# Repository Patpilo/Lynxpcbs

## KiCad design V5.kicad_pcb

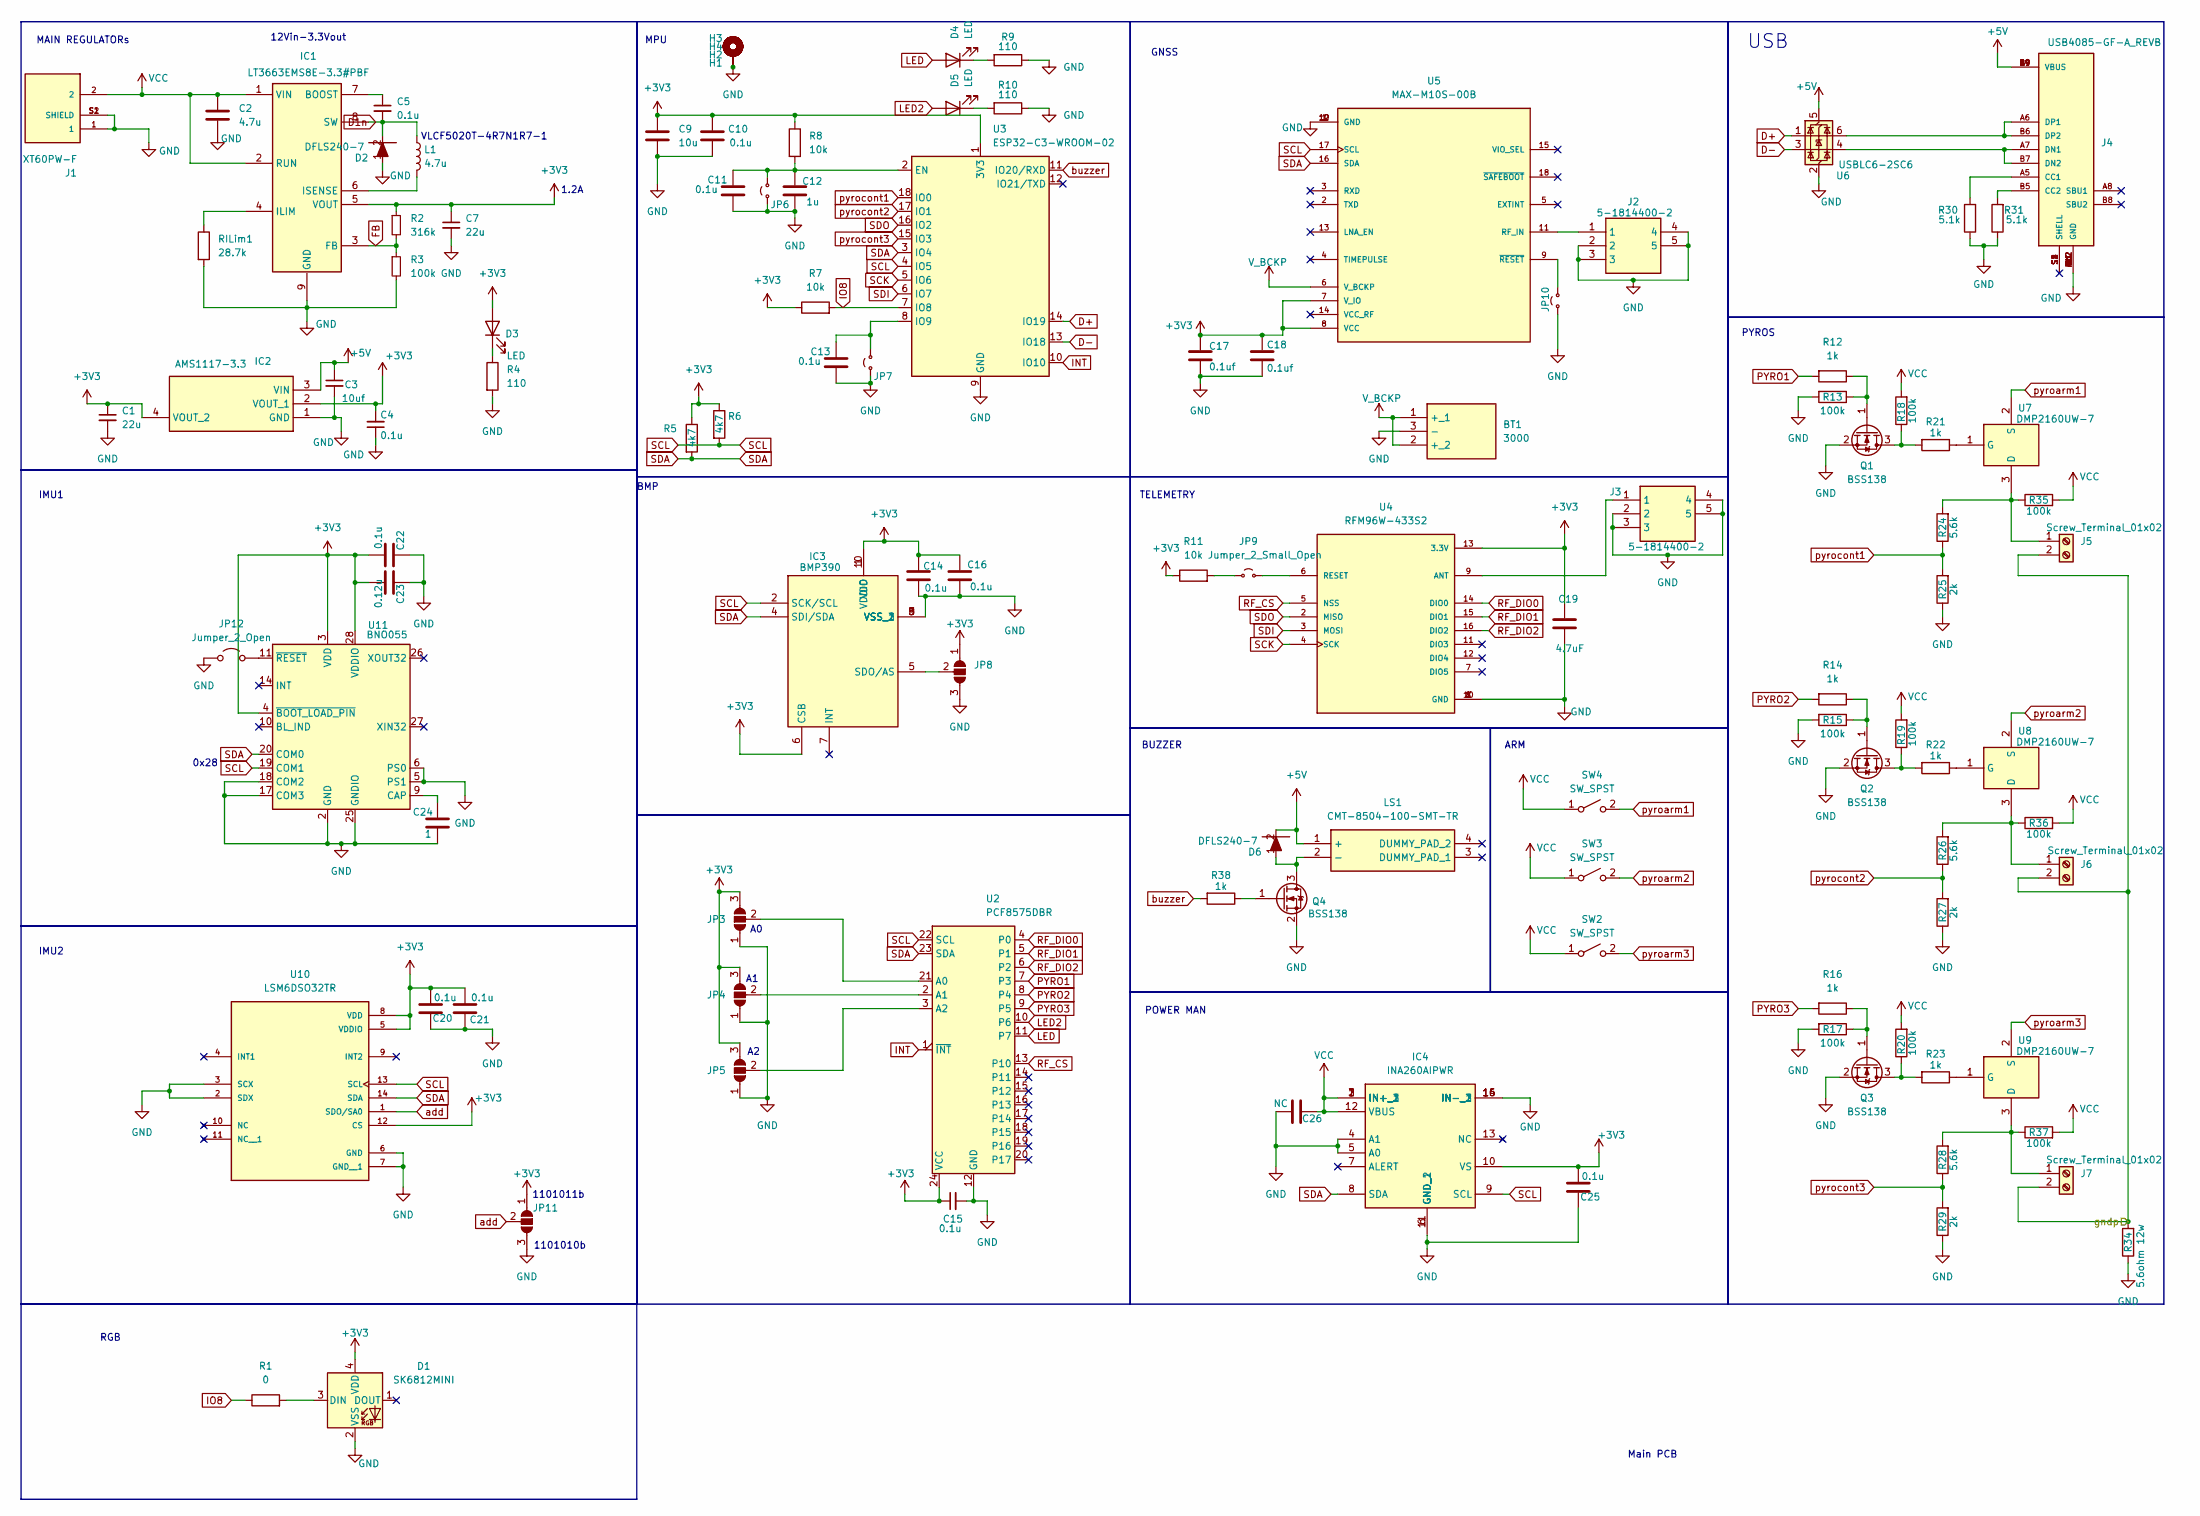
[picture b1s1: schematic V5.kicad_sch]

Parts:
BT1: 3000; Manufacturer_Part_Number 3000; Mouser Part Number 534-3000
C1: 22u; C_0805_2012Metric_Pad1.18x1.45mm_HandSolder
C2: 4.7u; C_1206_3216Metric_Pad1.33x1.80mm_HandSolder
C3: 10uf; C_0805_2012Metric_Pad1.18x1.45mm_HandSolder
C4, C5, C10, C11, C13, C14, C15, C16, C21: 0.1u; C_0805_2012Metric_Pad1.18x1.45mm_HandSolder
C7: 22u; C_1206_3216Metric_Pad1.33x1.80mm_HandSolder
C9: 10u; C_0805_2012Metric_Pad1.18x1.45mm_HandSolder
C12: 1u; C_0805_2012Metric_Pad1.18x1.45mm_HandSolder
C17, C18: 0.1uf; C_0805_2012Metric_Pad1.18x1.45mm_HandSolder
C19: 4.7uF; C_1206_3216Metric_Pad1.33x1.80mm_HandSolder
C20, C22, C25: 0.1u; C_0201_0603Metric_Pad0.64x0.40mm_HandSolder
C23: 0.12u; C_0201_0603Metric_Pad0.64x0.40mm_HandSolder
C24: 1; C_0805_2012Metric_Pad1.18x1.45mm_HandSolder
C26: NC; C_0201_0603Metric_Pad0.64x0.40mm_HandSolder
D1: SK6812MINI; LED_SK6812MINI_PLCC4_3.5x3.5mm_P1.75mm
D2, D6: DFLS240-7; POWERDI123; Manufacturer_Part_Number DFLS240-7; Mouser Part Number 621-DFLS240-7
D3, D4, D5: LED; LED_0805_2012Metric_Pad1.15x1.40mm_HandSolder
H1, H2, H3, H4: MountingHole_Pad; MountingHole_2.7mm_M2.5_Pad_Via
IC1: LT3663EMS8E-3.3#PBF; SOP65P490X110-9N; Manufacturer_Part_Number LT3663EMS8E-3.3#PBF; Mouser Part Number 584-3663EMS8E-3.3PBF
IC2: AMS1117-3.3; SOT229P700X180-4N; Manufacturer_Part_Number AMS1117-3.3
IC3: BMP390; Manufacturer_Part_Number BMP390; Mouser Part Number 262-BMP390
IC4: INA260AIPWR; SOP65P640X120-16N; Manufacturer_Part_Number INA260AIPWR; Mouser Part Number 595-INA260AIPWR
J1: XT60PW-F; AMASS_XT60PW-F; PARTREV V1.2
J2, J3: 5-1814400-2; 518144002; Manufacturer_Part_Number 5-1814400-2; Mouser Part Number 571-5-1814400-2
J4: USB4085-GF-A_REVB; GCT_USB4085-GF-A_REVB; PARTREV B
J5, J6, J7: Screw_Terminal_01x02; 2828362
JP3, JP4, JP5, JP8, JP11: SolderJumper_3_Open; SolderJumper-3_P1.3mm_Open_RoundedPad1.0x1.5mm_NumberLabels
JP6, JP7, JP9, JP10: Jumper_2_Small_Open; SolderJumper-2_P1.3mm_Open_RoundedPad1.0x1.5mm
JP12: Jumper_2_Open; SolderJumper-2_P1.3mm_Open_RoundedPad1.0x1.5mm
L1: 4.7u; VLCF5020
LS1: CMT-8504-100-SMT-TR; CMT8504100SMTTR; Manufacturer_Part_Number CMT-8504-100-SMT-TR; Mouser Part Number 490-CMT-8504100SMTTR
Q1, Q2, Q3, Q4: BSS138; SOT-23
R1: 0; R_0805_2012Metric_Pad1.20x1.40mm_HandSolder
R2: 316k; R_0805_2012Metric_Pad1.20x1.40mm_HandSolder
R3, R13, R15, R17, R18, R19, R20: 100k; R_0805_2012Metric_Pad1.20x1.40mm_HandSolder
R4, R9, R10: 110; R_0805_2012Metric_Pad1.20x1.40mm_HandSolder
R5, R6: 4k7; R_0805_2012Metric_Pad1.20x1.40mm_HandSolder
R7, R8, R11: 10k; R_0805_2012Metric_Pad1.20x1.40mm_HandSolder
R12, R14, R16, R21, R22, R23: 1k; R_0402_1005Metric_Pad0.72x0.64mm_HandSolder
R24, R26, R28: 5.6k; R_0402_1005Metric_Pad0.72x0.64mm_HandSolder
R25, R27, R29: 2k; R_0402_1005Metric_Pad0.72x0.64mm_HandSolder
R30, R31: 5.1k; R_0402_1005Metric_Pad0.72x0.64mm_HandSolder
R34: 5.6ohm 12w; R_2512_6332Metric_Pad1.40x3.35mm_HandSolder
R35, R36, R37: 100k; R_0603_1608Metric_Pad0.98x0.95mm_HandSolder
R38: 1k; R_0805_2012Metric_Pad1.20x1.40mm_HandSolder
RILim1: 28.7k; R_0805_2012Metric_Pad1.20x1.40mm_HandSolder
SW2, SW3, SW4: SW_SPST; ET02MD1CBE
U2: PCF8575DBR; SSOP-24_5.3x8.2mm_P0.65mm
U3: ESP32-C3-WROOM-02
U4: RFM96W-433S2; MODULE_RFM96W-433S2; PARTREV 2.0
U5: MAX-M10S-00B; XCVR_MAX-M10S-00B; PARTREV C1
U6: USBLC6-2SC6; SOT-23-6
U7, U8, U9: DMP2160UW-7; SOT65P210X110-3N; Manufacturer_Part_Number DMP2160UW-7; Mouser Part Number 621-DMP2160UW-7
U10: LSM6DSO32TR; LGA-14L_2P5X3X0P83_STM; PARTREV 1
U11: BNO055; LGA-28_5.2x3.8mm_P0.5mm

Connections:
+3V3: C1.1, C4.2, C7.1, C9.1, C10.1, C14.1, C15.1, C16.1, C17.1, C18.1, C19.1, C20.1, C21.1, C22.1, C23.1, C25.1, D1.4 (VDD), D3.2 (A), IC1.5 (VOUT), IC2.2 (VOUT_1), IC2.4 (VOUT_2), IC3.1 (VDDIO), IC3.6 (CSB), IC3.10 (VDD), IC4.10 (VS), JP3.3 (B), JP4.3 (B), JP5.3 (B), JP8.1 (A), JP11.1 (A), R2.1, R5.1, R6.1, R7.1, R8.1, R11.1, U2.24 (VCC), U3.1 (3V3), U4.13 (3.3V), U5.7 (V_IO), U5.8 (VCC), U10.5 (VDDIO), U10.8 (VDD), U10.12 (CS), U11.3 (VDD), U11.4 (~BOOT_LOAD_PIN), U11.28 (VDDIO)
+5V: C3.1, D6.2 (K), IC2.3 (VIN), J4.A4 (VBUS), J4.A9 (VBUS), J4.B4 (VBUS), J4.B9 (VBUS), LS1.1 (+), U6.5 (VBUS)
/gndp: J5.2, J6.2, J7.2, R34.2
D1n: C5.2, D2.2 (K), IC1.8 (SW), L1.1
D+: U3.14 (IO19), U6.1 (I/O1)
D-: U3.13 (IO18), U6.3 (I/O2)
FB: IC1.3 (FB), R2.2, R3.1
GND: BT1.3 (-), C1.2, C2.2, C3.2, C4.1, C7.2, C9.2, C10.2, C11.2, C12.2, C13.2, C14.2, C15.2, C16.2, C17.2, C18.2, C19.2, C20.2, C21.2, C22.2, C23.2, C24.1, C25.2, C26.1, D1.2 (VSS), D2.1 (A), H1.1, H2.1, H3.1, H4.1, IC1.9 (GND), IC2.1 (GND), IC3.3 (VSS_1), IC3.8 (VSS_2), IC3.9 (VSS_3), IC4.4 (A1), IC4.5 (A0), IC4.6 (GND_1), IC4.11 (GND_2), IC4.14 (IN-_1), IC4.15 (IN-_2), IC4.16 (IN-_3), J1.1, J1.S1 (SHIELD), J1.S2 (SHIELD), J2.2, J2.3, J2.4, J2.5, J3.2, J3.3, J3.4, J3.5, J4.A1 (GND), J4.A12 (GND), J4.B1 (GND), J4.B12 (GND), JP3.1 (A), JP4.1 (A), JP5.1 (A), JP6.1 (A), JP7.1 (A), JP8.3 (B), JP10.1 (A), JP11.3 (B), JP12.1 (A), Q1.2 (S), Q2.2 (S), Q3.2 (S), Q4.2 (S), R3.2, R4.2, R9.1, R10.1, R13.2, R15.2, R17.2, R25.1, R27.1, R29.1, R30.1, R31.1, R34.1, RILim1.2, U2.12 (GND), U3.9 (GND), U3.19 (GND), U4.1 (GND), U4.8 (GND), U4.10 (GND), U5.1 (GND), U5.10 (GND), U5.12 (GND), U6.2 (GND), U10.2 (SDX), U10.3 (SCX), U10.6 (GND), U10.7 (GND__1), U11.2 (GND), U11.5 (PS1), U11.6 (PS0), U11.17 (COM3), U11.18 (COM2), U11.25 (GNDIO)
INT: U2.1 (~INT), U3.10 (IO10)
IO8: R1.1, R7.2, U3.7 (IO8)
LED: D4.2 (A), U2.11 (P7)
LED2: D5.2 (A), U2.10 (P6)
unnamed: D1.3 (DIN), R1.2
unnamed: D3.1 (K), R4.1
unnamed: D4.1 (K), R9.2
unnamed: D5.1 (K), R10.2
unnamed: D6.1 (A), LS1.2 (-), Q4.3 (D)
unnamed: C5.1, IC1.7 (BOOST)
unnamed: IC1.4 (ILIM), RILim1.1
unnamed: IC1.6 (ISENSE), L1.2
unnamed: IC3.5 (SDO/AS), JP8.2 (C)
unnamed: J4.A5 (CC1), R30.2
unnamed: J4.B5 (CC2), R31.2
unnamed: J4.A7 (DN1), J4.B7 (DN2), U6.4 (I/O2)
unnamed: J4.A6 (DP1), J4.B6 (DP2), U6.6 (I/O1)
unnamed: J5.1, R24.2, R35.1, U7.3 (D)
unnamed: J6.1, R26.2, R36.1, U8.3 (D)
unnamed: J7.1, R28.2, R37.1, U9.3 (D)
unnamed: JP3.2 (C), U2.21 (A0)
unnamed: JP4.2 (C), U2.2 (A1)
unnamed: JP5.2 (C), U2.3 (A2)
unnamed: C11.1, C12.1, JP6.2 (B), R8.2, U3.2 (EN)
unnamed: C13.1, JP7.2 (B), U3.8 (IO9)
unnamed: JP9.1 (A), R11.2
unnamed: JP9.2 (B), U4.6 (RESET)
unnamed: JP10.2 (B), U5.9 (~RESET)
unnamed: JP12.2 (B), U11.11 (~RESET)
unnamed: Q1.3 (D), R18.1, R21.2
unnamed: Q1.1 (G), R12.1, R13.1
unnamed: Q2.3 (D), R19.1, R22.2
unnamed: Q2.1 (G), R14.1, R15.1
unnamed: Q3.3 (D), R20.1, R23.2
unnamed: Q3.1 (G), R16.1, R17.1
unnamed: Q4.1 (G), R38.1
unnamed: J3.1, U4.9 (ANT)
unnamed: J2.1, U5.11 (RF_IN)
unnamed: R21.1, U7.1 (G)
unnamed: R22.1, U8.1 (G)
unnamed: R23.1, U9.1 (G)
unnamed: C24.2, U11.9 (CAP)
PYRO1: R12.2, U2.7 (P3)
PYRO2: R14.2, U2.8 (P4)
PYRO3: R16.2, U2.9 (P5)
RF_CS: U2.13 (P10), U4.5 (NSS)
RF_DIO0: U2.4 (P0), U4.14 (DIO0)
RF_DIO1: U2.5 (P1), U4.15 (DIO1)
RF_DIO2: U2.6 (P2), U4.16 (DIO2)
SCK: U3.5 (IO6), U4.4 (SCK)
SCL: IC3.2 (SCK/SCL), IC4.9 (SCL), R6.2, U2.22 (SCL), U3.4 (IO5), U5.17 (SCL), U10.13 (SCL), U11.19 (COM1)
SDA: IC3.4 (SDI/SDA), IC4.8 (SDA), R5.2, U2.23 (SDA), U3.3 (IO4), U5.16 (SDA), U10.14 (SDA), U11.20 (COM0)
SDI: U3.6 (IO7), U4.3 (MOSI)
SDO: U3.16 (IO2), U4.2 (MISO)
VCC: C2.1, C26.2, IC1.1 (VIN), IC1.2 (RUN), IC4.1 (IN+_1), IC4.2 (IN+_2), IC4.3 (IN+_3), IC4.12 (VBUS), J1.2, R18.2, R19.2, R20.2, R35.2, R36.2, R37.2, SW2.1 (A), SW3.1 (A), SW4.1 (A)
V_BCKP: BT1.1 (+_1), BT1.2 (+_2), U5.6 (V_BCKP)
add: JP11.2 (C), U10.1 (SDO/SA0)
buzzer: R38.2, U3.11 (IO20/RXD)
pyroarm1: SW4.2 (B), U7.2 (S)
pyroarm2: SW3.2 (B), U8.2 (S)
pyroarm3: SW2.2 (B), U9.2 (S)
pyrocont1: R24.1, R25.2, U3.18 (IO0)
pyrocont2: R26.1, R27.2, U3.17 (IO1)
pyrocont3: R28.1, R29.2, U3.15 (IO3)

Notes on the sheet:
IMU2
0x28
POWER MAN
1101010b
MPU
PYROS
1.2A
ARM
12Vin-3.3Vout
Main PCB
IMU1
BMP
TELEMETRY
GNSS
BUZZER
1101011b
RGB
VLCF5020T-4R7N1R7-1
MAIN REGULATORs
USB

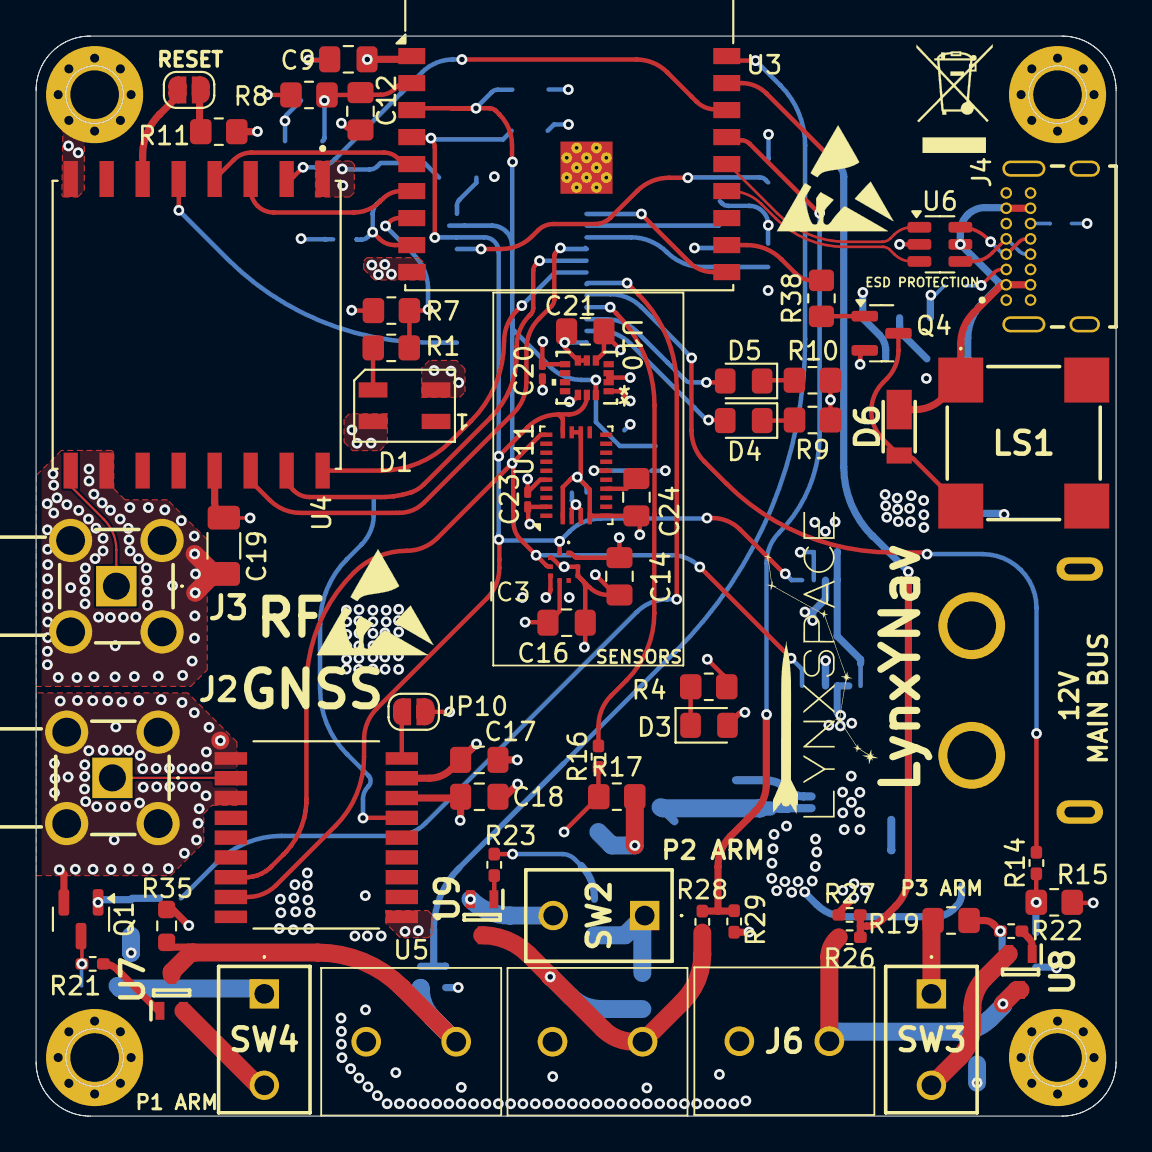
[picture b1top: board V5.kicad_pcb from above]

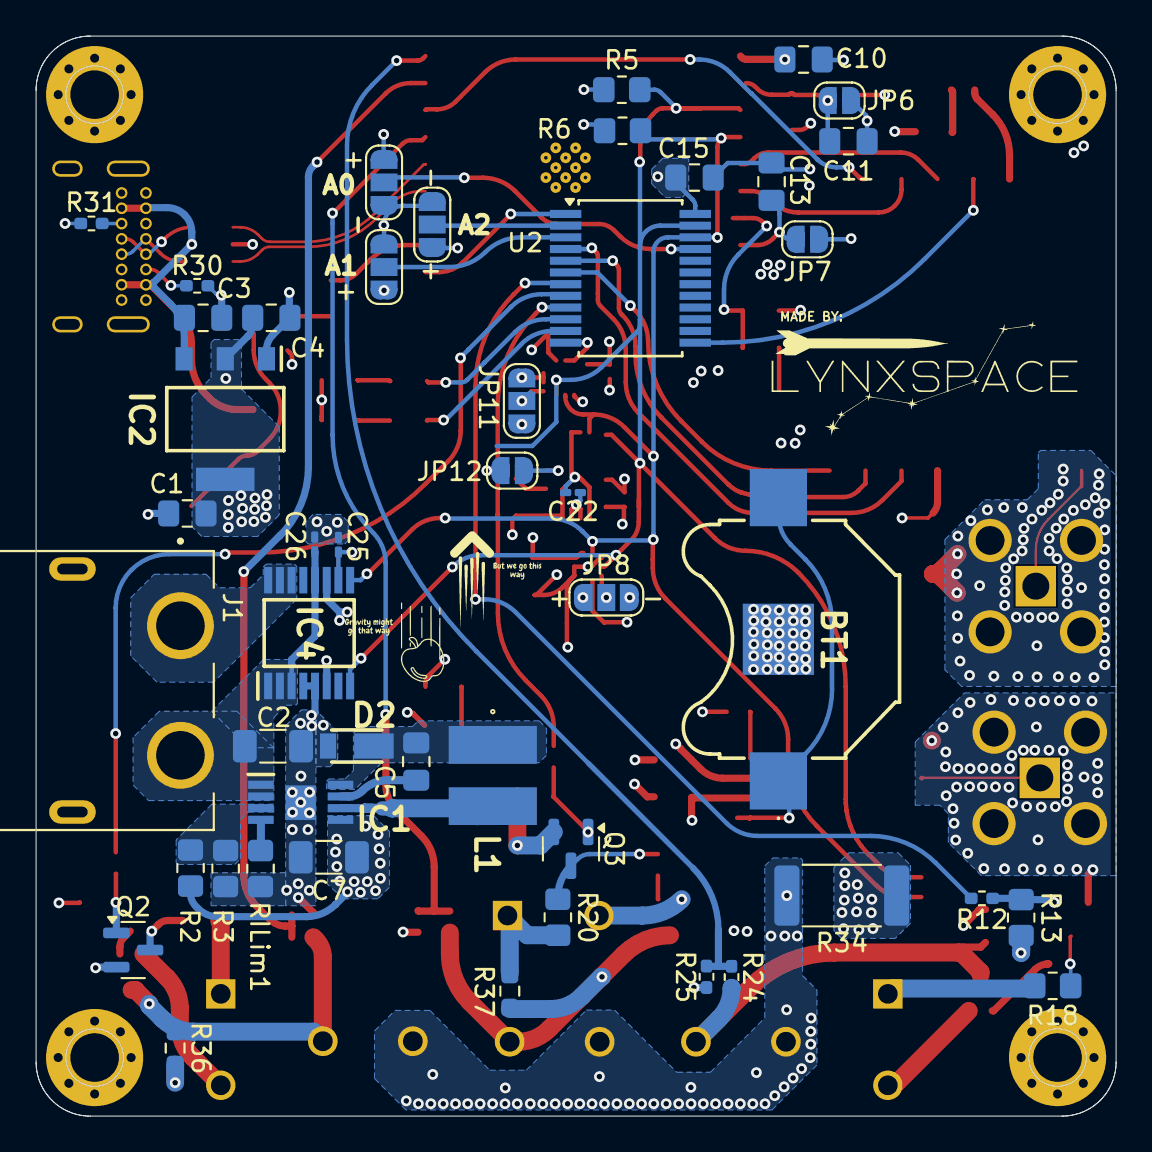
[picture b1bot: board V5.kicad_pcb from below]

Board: 4 copper layers, 60.0 x 60.0 mm, 112 parts (47 on the bottom side), 72 nets.

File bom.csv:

Designator,Footprint,Quantity,Value,LCSC Part #
BT1,3000,1,3000,
C1,0805,1,22u,
"C10, C11, C13, C14, C15, C16, C21, C4, C5",0805,9,0.1u,
C12,0805,1,1u,
"C17, C18",0805,2,0.1uf,
C19,1206,1,4.7uF,
C2,1206,1,4.7u,
"C20, C22",0201,2,0.1u,
C23,0201,1,0.12u,
C24,0805,1,1,
C3,0805,1,10uf,
C7,1206,1,22u,
C9,0805,1,10u,
D1,LED_SK6812MINI_PLCC4_3.5x3.5mm_P1.75mm,1,SK6812MINI,
"D2, D6",POWERDI123,2,DFLS240-7,
"D3, D4, D5",0805,3,LED,
IC1,SOP65P490X110-9N,1,LT3663EMS8E-3.3#PBF,
IC2,SOT229P700X180-4N,1,AMS1117-3.3,
IC3,BMP390,1,BMP390,
J1,AMASS_XT60PW-F,1,XT60PW-F,
"J2, J3",518144002,2,5-1814400-2,
J4,GCT_USB4085-GF-A_REVB,1,USB4085-GF-A_REVB,
"J5, J6, J7",2828362,3,Screw_Terminal_01x02,
"JP10, JP6, JP7, JP9",SolderJumper-2_P1.3mm_Open_RoundedPad1.0x1.5mm,4,Jumper_2_Small_Open,
JP12,SolderJumper-2_P1.3mm_Open_RoundedPad1.0x1.5mm,1,Jumper_2_Open,
L1,VLCF5020,1,4.7u,
LS1,CMT8504100SMTTR,1,CMT-8504-100-SMT-TR,
"Q1, Q2, Q3, Q4",SOT-23,4,BSS138,
R1,0805,1,0,
"R10, R4, R9",0805,3,110,
"R11, R7, R8",0805,3,10k,
"R12, R14, R16, R21, R22, R23, R38",0805,7,1k,
"R13, R15, R17, R18, R19, R20, R3, R35, R36, R37",0805,10,100k,
R2,0805,1,316k,
"R24, R26, R28",0805,3,5.6k,
"R25, R27, R29",0805,3,2k,
"R30, R31",0402,2,5.1k,
R34,2512,1,5.6ohm 12w,
"R5, R6",0805,2,4k7,
RILIM1,0805,1,28.7k,
SW1,MN11LL1W01-C,1,SW_SPST,
"SW2, SW3, SW4",ET02MD1CBE,3,SW_SPST,
U10,LGA-14L_2P5X3X0P83_STM,1,LSM6DSO32TR,
U11,LGA-28_5.2x3.8mm_P0.5mm,1,BNO055,
U2,SSOP-24_5.3x8.2mm_P0.65mm,1,PCF8575DBR,
U3,ESP32-C3-WROOM-02,1,ESP32-C3-WROOM-02,
U4,MODULE_RFM96W-433S2,1,RFM96W-433S2,
U5,XCVR_MAX-M10S-00B,1,MAX-M10S-00B,
U6,SOT-23-6,1,USBLC6-2SC6,
"U7, U8, U9",SOT65P210X110-3N,3,DMP2160UW-7,

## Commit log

2024-10-13 Update V3
2025-04-03 A
    A
2025-04-03 V5v2
